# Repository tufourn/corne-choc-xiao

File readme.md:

# Choc-spaced Corne keyboard with XIAO BLE and LIR2032
* Gerbers: [Gerbers](https://github.com/tufourn/corne-choc-xiao/blob/hotswap/corne-hotswap.zip?raw=true)
* Interactive bill of materials: [iBOM](https://htmlpreview.github.io/?https://github.com/tufourn/corne-choc-xiao/blob/hotswap/bom/ibom.html)

## PCB

A choc-spaced Corne PCB modified to support LIR2032 batteries and XIAO BLE microcontroller.

Supports optional hotswap sockets.

Ordering from [JLCPCB](https://www.jlcpcb.com) will cost about $8 + shipping.

## Bill of materials

| Name | Qty | Package | Value | Description |
| ---- | --- | ------- | ----- |------------ |
| U1   | 1   | SMD     | MCU   | XIAO BLE    |
| U2   | 1   | SOT-23-6| DW01A |Battery protection IC |
| U3   | 1   | TSSOP-8 | FS8205A | Dual N-Channel MOSFET |
| C1   | 1   | 0603    | 100n | SMD Capacitor |
| R1   | 1   | 0603    | 100R | SMD Resistor |
| R2   | 1   | 0603    | 1k   | SMD Resistor |
| Q1   | 1   | SOT-23  | SI2302 | N-channel MOSFET for reverse polarity protection |
| S1   | 1   | SMD     | SPDT | 7 pin SMD SPDT Switch |
| BT1  | 1   | SMD     | LIR2032 | LIR2032 Battery Retainer |
| D1-36| 36  | SOT-123 | 1n4148 | Diodes for keyboard matrix |
| SW1-36 | 36| THT     | PG1350 | Kailh Choc Switches |

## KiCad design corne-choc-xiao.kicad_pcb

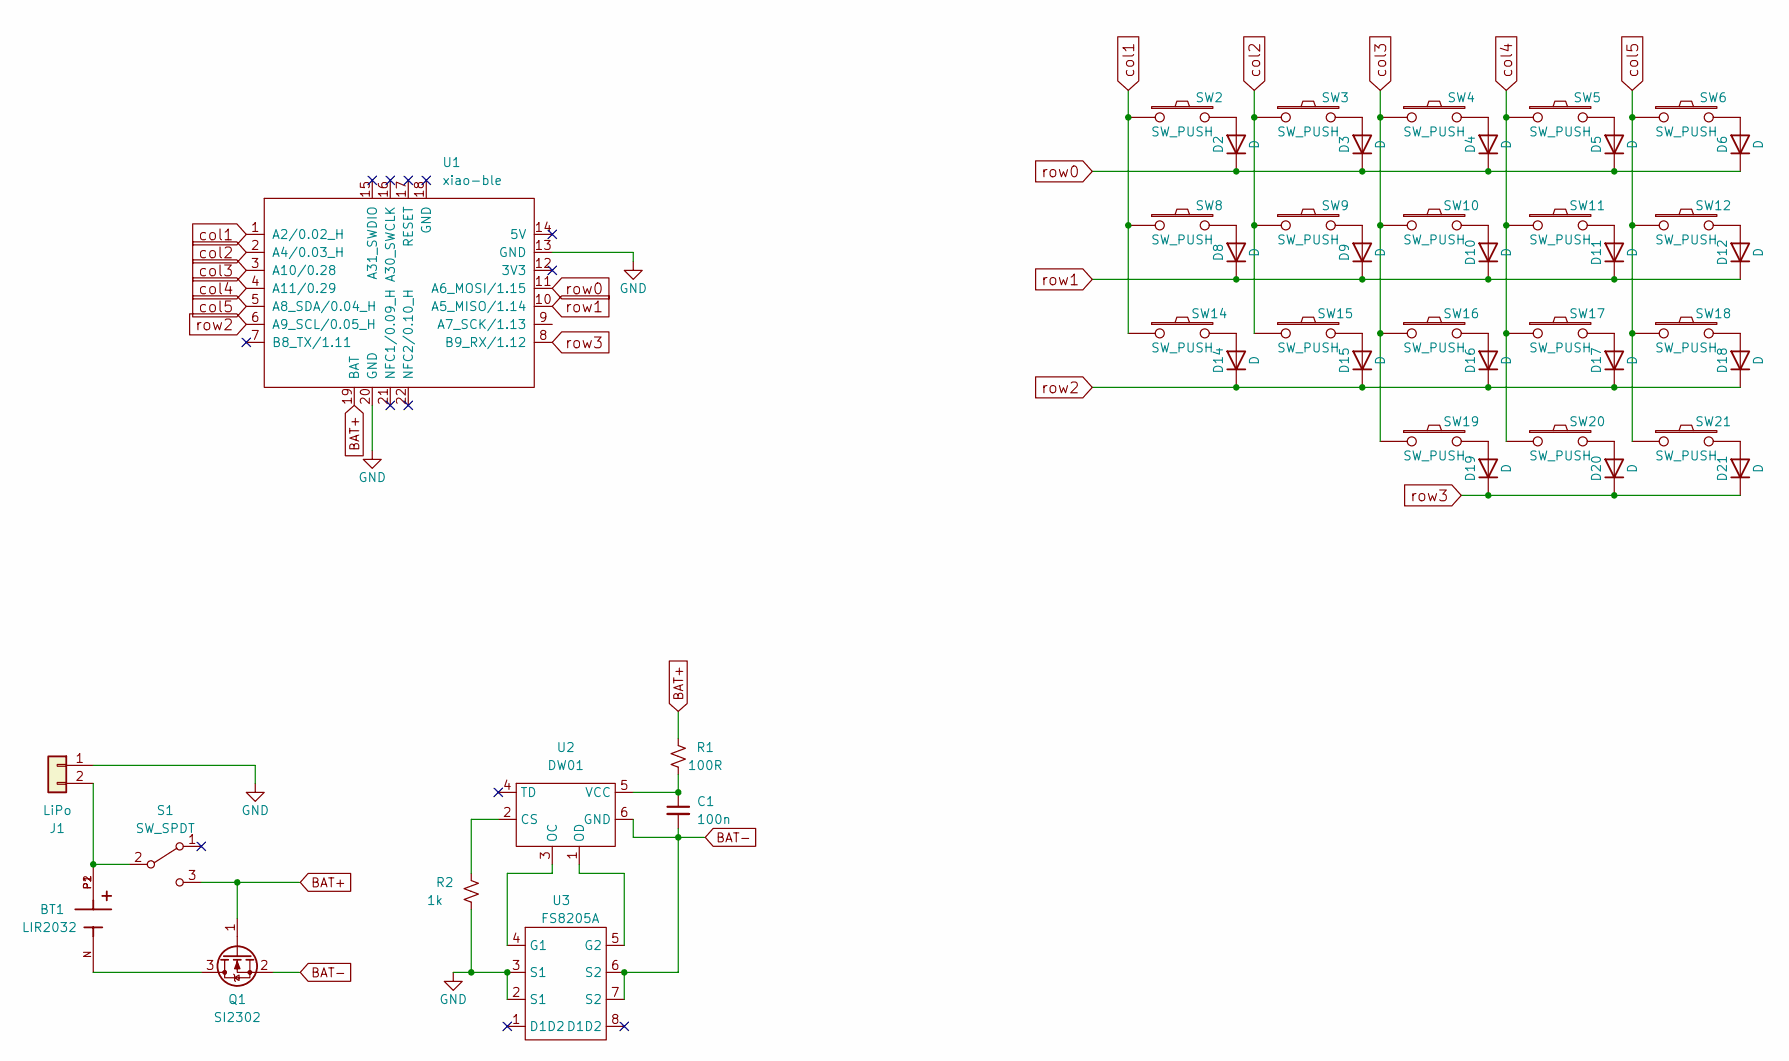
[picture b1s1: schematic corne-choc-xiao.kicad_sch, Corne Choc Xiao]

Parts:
BT1: LIR2032; BAT_3002; PARTREV A
C1: 100n; C_0603_1608Metric_Pad1.08x0.95mm_HandSolder
D2, D3, D4, D5, D6, D8, D9, D10, D11, D12, D14, D15, D16, D17, D18, D19, D20, D21: D; SOD-123-TH
J1: LiPo; JST_PH_S2B-PH-K_1x02_P2.00mm_Horizontal
Q1: SI2302; SOT-23
R1: 100R; R_0603_1608Metric_Pad0.98x0.95mm_HandSolder
R2: 1k; R_0603_1608Metric_Pad0.98x0.95mm_HandSolder
S1: SW_SPDT; SW_SPDT_PCM12
SW2, SW3, SW4, SW5, SW6, SW8, SW9, SW10, SW11, SW12, SW14, SW15, SW16, SW17, SW18, SW19, SW20, SW21: SW_PUSH; Kailh_socket_PG1350_optional_reversible
U1: xiao-ble; xiao-ble-tht-cutout
U2: DW01; SOT-23-6
U3: FS8205A; TSSOP-8_4.4x3mm_P0.65mm

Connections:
BAT+: Q1.1 (G), R1.2, S1.3 (C), U1.19 (BAT)
BAT-: C1.2, Q1.2 (S), U2.6 (GND), U3.6 (S2), U3.7 (S2)
GND: J1.1, R2.2, U1.13 (GND), U1.20 (GND), U3.2 (S1), U3.3 (S1)
unnamed: D2.2 (A), SW2.2
unnamed: D3.2 (A), SW3.2
unnamed: D4.2 (A), SW4.2
unnamed: D5.2 (A), SW5.2
unnamed: D6.2 (A), SW6.2
unnamed: D8.2 (A), SW8.2
unnamed: D9.2 (A), SW9.2
unnamed: D10.2 (A), SW10.2
unnamed: D11.2 (A), SW11.2
unnamed: D12.2 (A), SW12.2
unnamed: D14.2 (A), SW14.2
unnamed: D15.2 (A), SW15.2
unnamed: D16.2 (A), SW16.2
unnamed: D17.2 (A), SW17.2
unnamed: D18.2 (A), SW18.2
unnamed: D19.2 (A), SW19.2
unnamed: D20.2 (A), SW20.2
unnamed: D21.2 (A), SW21.2
unnamed: BT1.P1, BT1.P2, J1.2, S1.2 (B)
unnamed: BT1.N, Q1.3 (D)
unnamed: R2.1, U2.2 (CS)
unnamed: U2.3 (OC), U3.4 (G1)
unnamed: U2.1 (OD), U3.5 (G2)
unnamed: C1.1, R1.1, U2.5 (VCC)
col1: SW2.1, SW8.1, SW14.1, U1.1 (A2/0.02_H)
col2: SW3.1, SW9.1, SW15.1, U1.2 (A4/0.03_H)
col3: SW4.1, SW10.1, SW16.1, SW19.1, U1.3 (A10/0.28)
col4: SW5.1, SW11.1, SW17.1, SW20.1, U1.4 (A11/0.29)
col5: SW6.1, SW12.1, SW18.1, SW21.1, U1.5 (A8_SDA/0.04_H)
row0: D2.1 (K), D3.1 (K), D4.1 (K), D5.1 (K), D6.1 (K), U1.11 (A6_MOSI/1.15)
row1: D8.1 (K), D9.1 (K), D10.1 (K), D11.1 (K), D12.1 (K), U1.10 (A5_MISO/1.14)
row2: D14.1 (K), D15.1 (K), D16.1 (K), D17.1 (K), D18.1 (K), U1.6 (A9_SCL/0.05_H)
row3: D19.1 (K), D20.1 (K), D21.1 (K), U1.8 (B9_RX/1.12)

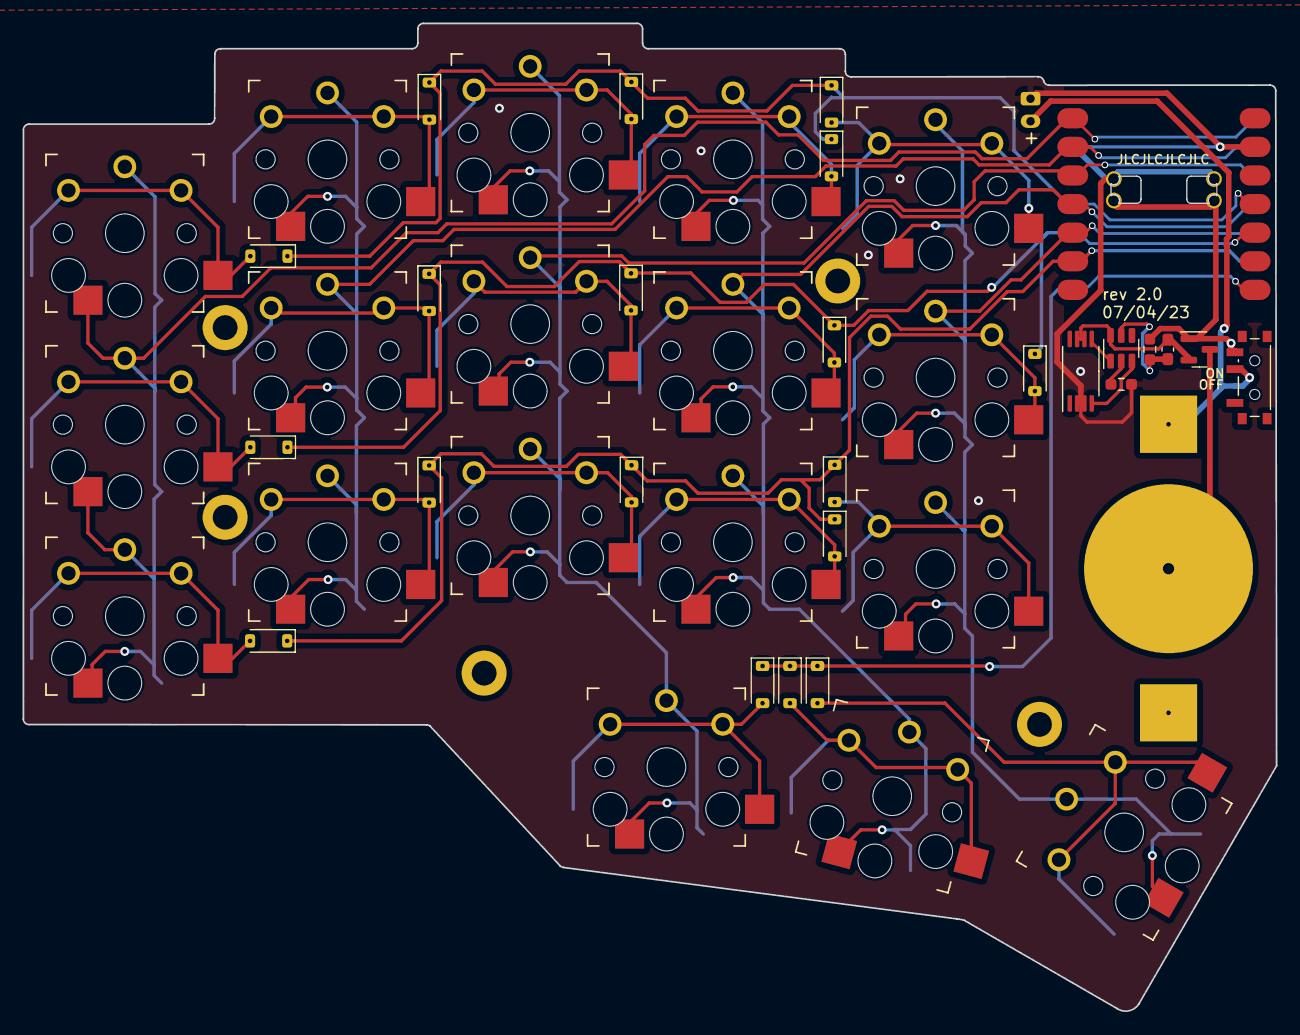
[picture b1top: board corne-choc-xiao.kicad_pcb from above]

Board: 2 copper layers, 111.3 x 87.7 mm, 49 parts (1 on the bottom side), 36 nets.

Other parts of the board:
h2, h2#2, h2#3: h2; LEGO_HOLE

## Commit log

2023-06-22 initial
2023-06-27 fix battery protection circuit
2023-07-04 added readme and ibom
2023-07-04 fix ibom link
2023-07-04 added hotswap and removed lipo connector
2023-07-04 generate gerbers
2023-07-04 regenerate gerbers
2023-07-05 readded lipo terminals
2023-07-21 updated ibom
